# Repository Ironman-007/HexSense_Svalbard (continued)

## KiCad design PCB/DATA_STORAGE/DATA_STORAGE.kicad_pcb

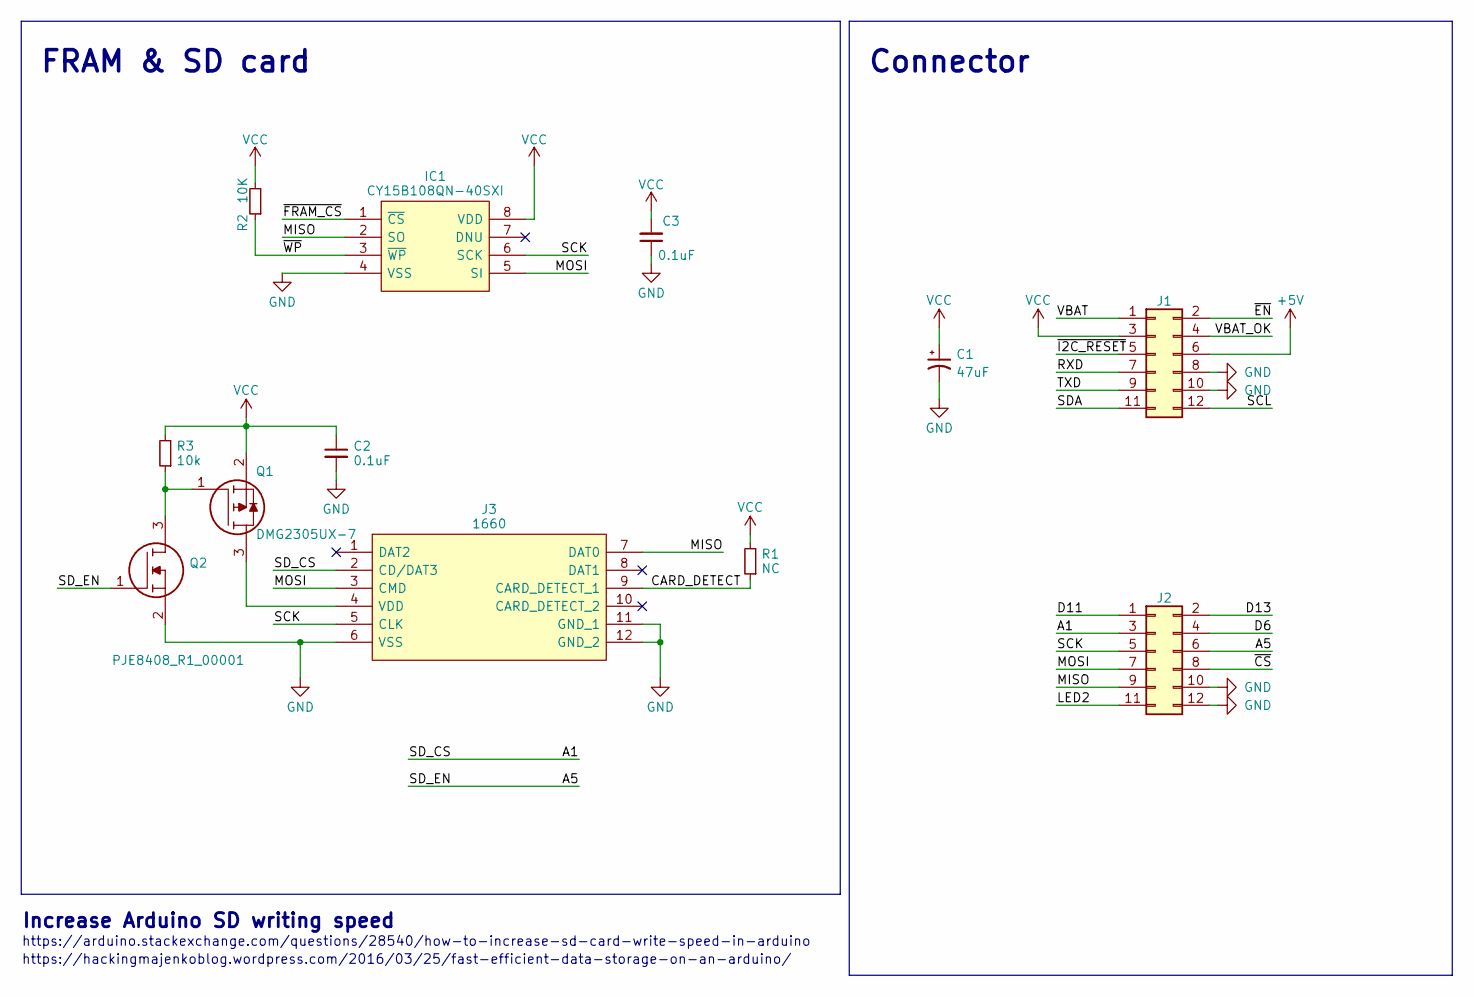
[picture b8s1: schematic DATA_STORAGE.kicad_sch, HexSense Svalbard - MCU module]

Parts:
C1: 47uF; LED_0805_2012Metric_Pad1.15x1.40mm_HandSolder
C2, C3: 0.1uF; C_0603_1608Metric_Pad1.08x0.95mm_HandSolder
IC1: CY15B108QN-40SXI; SOIC127P800X203-8N; Manufacturer_Part_Number CY15B108QN-40SXI; Mouser Part Number 727-CY15B108QN-40SXI
J1, J2: Conn_02x06_Odd_Even; PinHeader_2x06_P2.54mm_Vertical
J3: 1660; Manufacturer_Part_Number 1660; Mouser Part Number 485-1660
Q1: DMG2305UX-7; SOT96P240X110-3N; Manufacturer_Part_Number DMG2305UX-7; Mouser Part Number 621-DMG2305UX-7
Q2: PJE8408_R1_00001; SOTFL50P160X60-3N; Manufacturer_Part_Number PJE8408_R1_00001; Mouser Part Number 241-PJE8408_R1_00001
R1: NC; R_0603_1608Metric_Pad0.98x0.95mm_HandSolder
R2: 10K; R_0402_1005Metric_Pad0.72x0.64mm_HandSolder
R3: 10k; R_0603_1608Metric_Pad0.98x0.95mm_HandSolder

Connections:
+5V: J1.6
/A1: J2.3, J3.2 (CD/DAT3)
/A5: J2.6, Q2.1
/CARD_DETECT: J3.9 (CARD_DETECT_1), R1.1
/D6: J2.4
/D11: J2.1
/D13: J2.2
/LED2: J2.11
/MISO: IC1.2 (SO), J2.9, J3.7 (DAT0)
/MOSI: IC1.5 (SI), J2.7, J3.3 (CMD)
/RXD: J1.7
/SCK: IC1.6 (SCK), J2.5, J3.5 (CLK)
/SCL: J1.12
/SDA: J1.11
/TXD: J1.9
/VBAT: J1.1
/VBAT_OK: J1.4
/~CS: J2.8
/~EN: J1.2
/~FRAM_CS: IC1.1 (~CS)
/~I2C_RESET: J1.5
/~WP: IC1.3 (~WP), R2.1
GND: C1.2, C2.2, C3.1, IC1.4 (VSS), J1.8, J1.10, J2.10, J2.12, J3.6 (VSS), J3.11 (GND_1), J3.12 (GND_2), Q2.2
unnamed: J3.4 (VDD), Q1.3
unnamed: Q1.1, Q2.3, R3.1
VCC: C1.1, C2.1, C3.2, IC1.8 (VDD), J1.3, Q1.2, R1.2, R2.2, R3.2

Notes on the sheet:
https://arduino.stackexchange.com/questions/28540/how-to-increase-sd-card-write-speed-in-arduino
FRAM & SD card
Increase Arduino SD writing speed
https://hackingmajenkoblog.wordpress.com/2016/03/25/fast-efficient-data-storage-on-an-arduino/
Connector

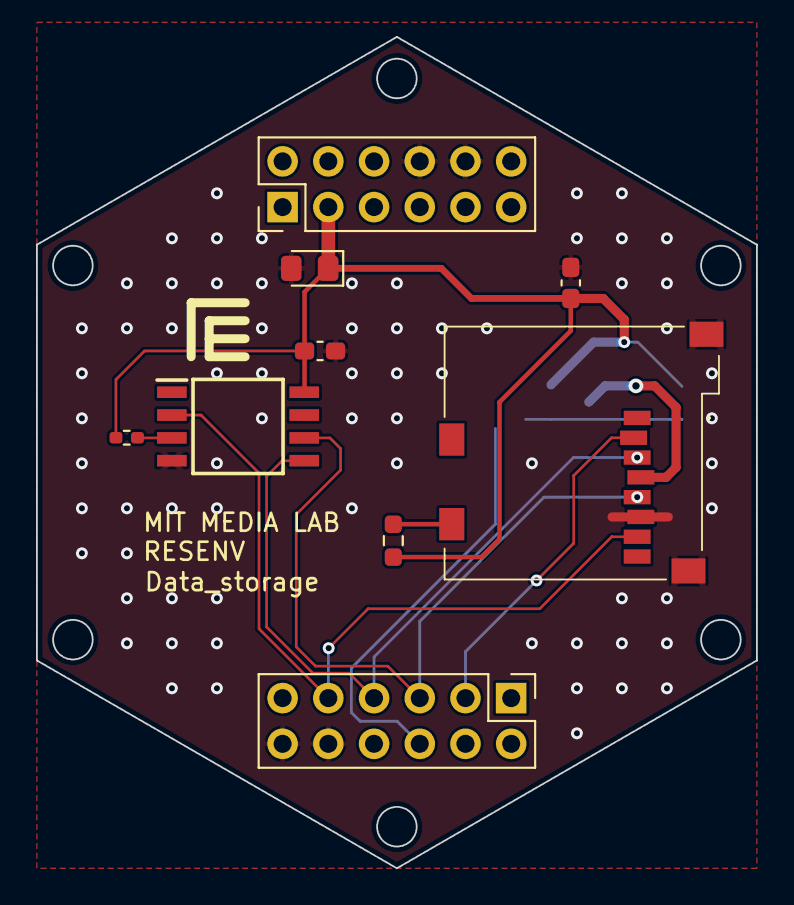
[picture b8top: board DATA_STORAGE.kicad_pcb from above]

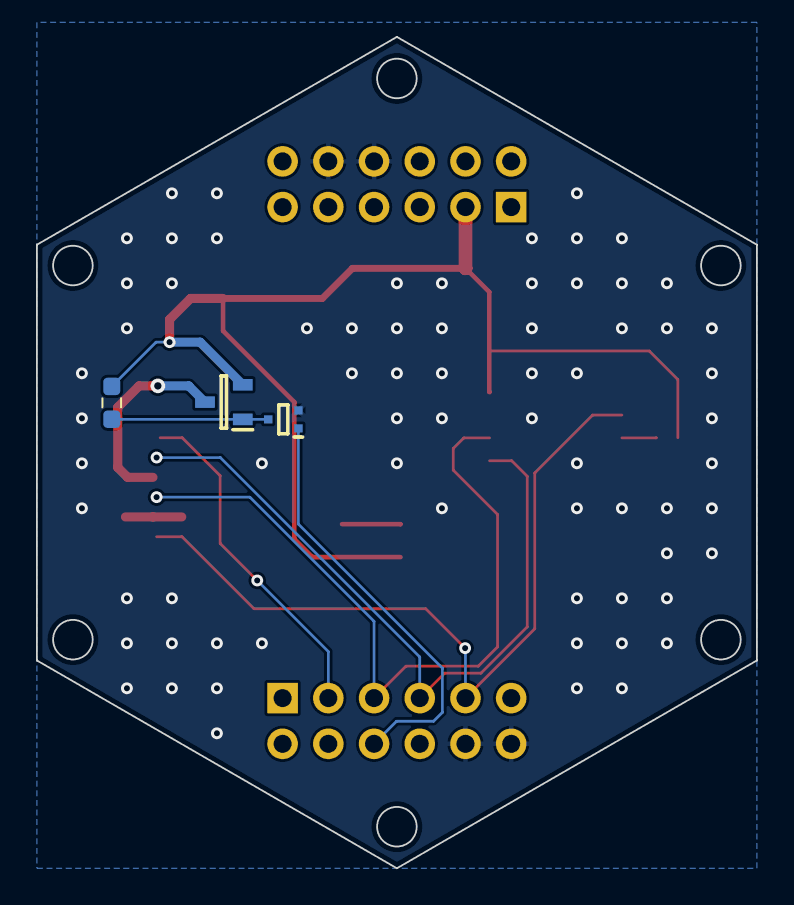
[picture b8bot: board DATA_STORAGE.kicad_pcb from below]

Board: 2 copper layers, 40.0 x 46.2 mm, 12 parts (3 on the bottom side), 11 nets.

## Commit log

2023-05-18 udated by FZ from Mac
2023-05-21 udated by FZ from Windows
